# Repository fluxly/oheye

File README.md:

# oheye
Oh Eye for Raspberry Pi 

16 analog inputs for the Pi. Requires SPI to be enabled in the Pi's configuration. Uses two MCP3008 10-bit A to D converters.

There's a Python library on the Python Package Index (https://pypi.org/project/oheye/) that you can install from the command line with Pip:

<pre>  sudo pip install oheye</pre>
  
Take a look at the ohEyePython directory for a few examples:

<pre>
#!/usr/bin/python

from oheye import analog_in 
import time

while True:
    for i in range(15):
        value = analog_in.read(i)
        print "%4d" % value,
    time.sleep(0.2)
    print;
</pre>

You can also use the Pd example in that directory to use the ohEye from Pure Data. That requires the WiringPi Pd external:

 http://nyu-waverlylabs.org/rpi-gpio/

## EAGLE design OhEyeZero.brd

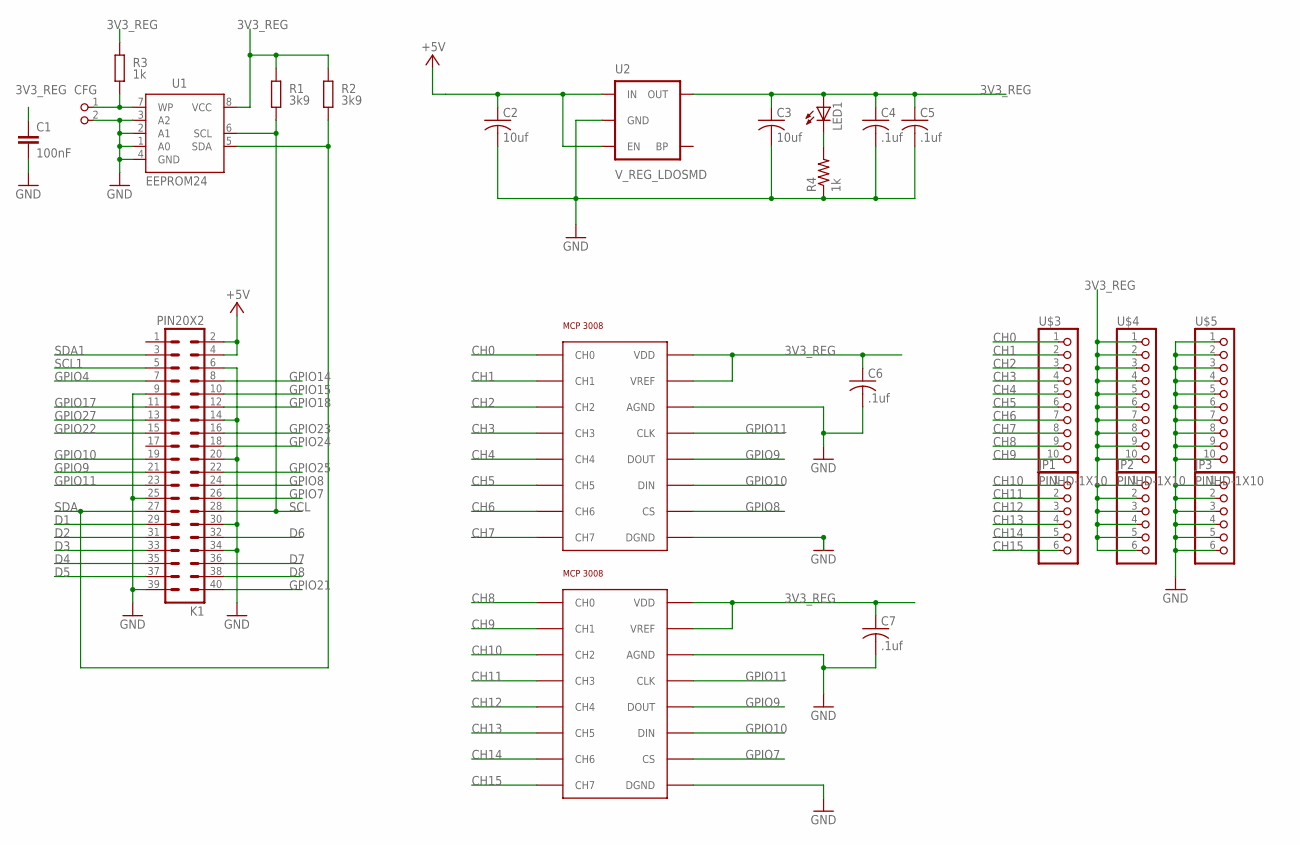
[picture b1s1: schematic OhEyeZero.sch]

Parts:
C1: 100nF; C0805K
C2, C3: 10uf; C0805K
C4, C5, C6, C7: .1uf; C0805K
CFG: PIN2_100; PIN_W_2
JP1, JP2, JP3: PINHD-1X6B; 1X06-BIG
K1: PIN20X2; PIN_20X2
LED1: LEDLED-0805; LED0805.PAC
R1, R2: 3k9; M0805; TOLERANCE 5%
R3: 1k; M0805; TOLERANCE 5%
R4: 1k; R0805W
U1: EEPROM24; SOIC8
U2: V_REG_LDOSMD; SOT23-5
U$1, U$2: MCP3008_ADC; SOIC16
U$3, U$4, U$5: PINHD-1X10; 1X10-BIG

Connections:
3V3_REG: C1.1, C3.1, C4.1, C5.1, C6.1, C7.1, JP2.1, JP2.2, JP2.3, JP2.4, JP2.5, JP2.6, LED1.A, R1.2, R2.2, R3.2, U1.8 (VCC), U2.5 (OUT), U$1.P$15 (VREF), U$1.P$16 (VDD), U$2.P$15 (VREF), U$2.P$16 (VDD), U$4.1, U$4.2, U$4.3, U$4.4, U$4.5, U$4.6, U$4.7, U$4.8, U$4.9, U$4.10
+5V: C2.1, K1.2, K1.4, U2.1 (IN), U2.3 (EN)
CH0: U$1.P$1 (CH0), U$3.1
CH1: U$1.P$2 (CH1), U$3.2
CH2: U$1.P$3 (CH2), U$3.3
CH3: U$1.P$4 (CH3), U$3.4
CH4: U$1.P$5 (CH4), U$3.5
CH5: U$1.P$6 (CH5), U$3.6
CH6: U$1.P$7 (CH6), U$3.7
CH7: U$1.P$8 (CH7), U$3.8
CH8: U$2.P$1 (CH0), U$3.9
CH9: U$2.P$2 (CH1), U$3.10
CH10: JP1.1, U$2.P$3 (CH2)
CH11: JP1.2, U$2.P$4 (CH3)
CH12: JP1.3, U$2.P$5 (CH4)
CH13: JP1.4, U$2.P$6 (CH5)
CH14: JP1.5, U$2.P$7 (CH6)
CH15: JP1.6, U$2.P$8 (CH7)
D1: K1.29
D2: K1.31
D3: K1.33
D4: K1.35
D5: K1.37
D6: K1.32
D7: K1.36
D8: K1.38
GND: C1.2, C2.2, C3.2, C4.2, C5.2, C6.2, C7.2, CFG.2, JP3.1, JP3.2, JP3.3, JP3.4, JP3.5, JP3.6, K1.6, K1.9, K1.14, K1.20, K1.25, K1.30, K1.34, K1.39, R4.1, U1.1 (A0), U1.2 (A1), U1.3 (A2), U1.4 (GND), U2.2 (GND), U$1.P$9 (DGND), U$1.P$14 (AGND), U$2.P$9 (DGND), U$2.P$14 (AGND), U$5.1, U$5.2, U$5.3, U$5.4, U$5.5, U$5.6, U$5.7, U$5.8, U$5.9, U$5.10
GPIO4: K1.7
GPIO7: K1.26, U$2.P$10 (CS)
GPIO8: K1.24, U$1.P$10 (CS)
GPIO9: K1.21, U$1.P$12 (DOUT), U$2.P$12 (DOUT)
GPIO10: K1.19, U$1.P$11 (DIN), U$2.P$11 (DIN)
GPIO11: K1.23, U$1.P$13 (CLK), U$2.P$13 (CLK)
GPIO14: K1.8
GPIO15: K1.10
GPIO17: K1.11
GPIO18: K1.12
GPIO21: K1.40
GPIO22: K1.15
GPIO23: K1.16
GPIO24: K1.18
GPIO25: K1.22
GPIO27: K1.13
unnamed: CFG.1, R3.1, U1.7 (WP)
unnamed: LED1.K (C), R4.2
SCL: K1.28, R1.1, U1.6 (SCL)
SCL1: K1.5
SDA: K1.27, R2.1, U1.5 (SDA)
SDA1: K1.3

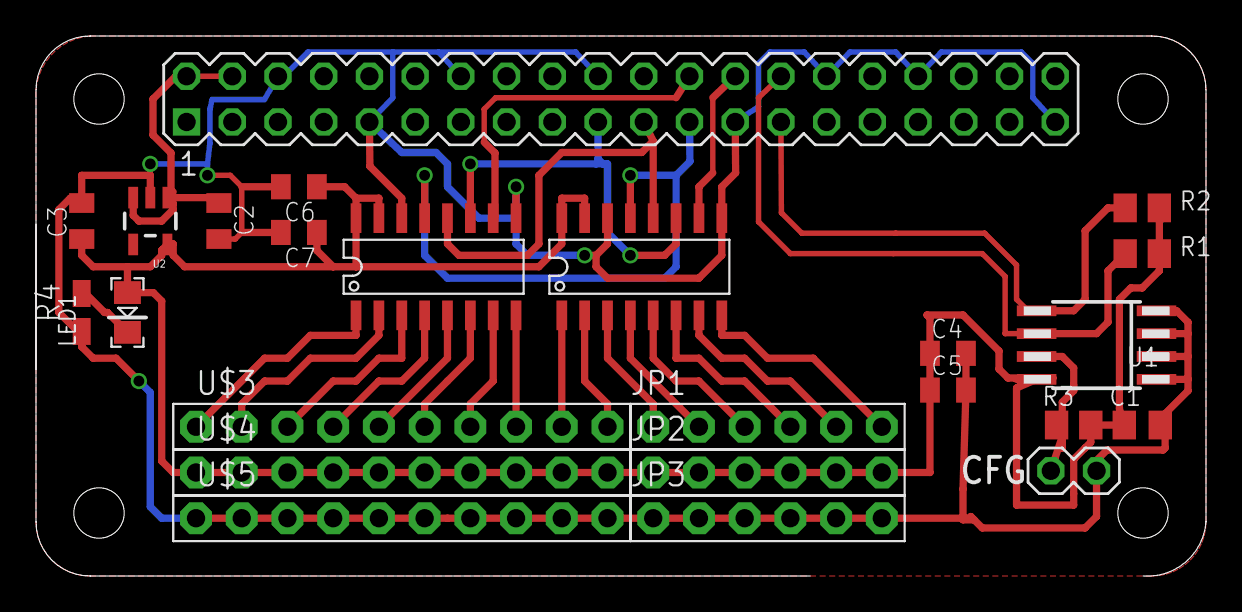
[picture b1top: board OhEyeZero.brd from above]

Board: 2 copper layers, 65.0 x 30.0 mm, 24 parts (0 on the bottom side), 28 nets.

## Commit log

2020-01-20 updated examples and pypi egg
